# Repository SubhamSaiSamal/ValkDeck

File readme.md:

# VALKDECK 

Hey there, I'm Subham, a 14 year old kid (currently) from Chennai, India

I needed a better way to manage my flight sim telemetry, trigered automation workflows, and also blindly control my volume while locked into a game. I could have bought a generic macropad off Amazon for $20.

Instead, I spent 40 hours learning KiCad, routing my own custom PCB, designing an enclosure in onshape, and writing a CircuitPython program from scratch.

Welcome to *ValkDeck.*

It's a 9-key, fully hotswappable cyberdeck module powered by a Raspberry Pi Pico. It features per=key WS2812B underglow, a rotary encoder for media control, and a 0.91" I2C OLED display that feeds back live system status so I can actually know what my macros are doing.

# FEATURE PIVOT

If you look at the top right of the board, you'll see a machined metal blanking plug.

Originally, that 12mm hole was meant for a massive, avionics-grade MTS-101 toggle switch (the "Nuke Switch") to act as a hardware reset. I measured the top plate perfectly. What i *forgot* to measure was the internal Z-axis clearance. The massive rectangular block of the toggle switch slammed right into the PCB.

Physical reality remains undefeated. Instead of spending the next 6 hours rearranging the whole top-case, I pivoted. I covered it with a sleek metal plug for a premium industrial look. It's not a bug; it's an aesthetic hardware change.

[OnshapeCase](https://cad.onshape.com/documents/f17dd9f4e6cb3dbe968d54ad/w/35238b8d1c489f2cc410f163/e/0b39d0bd7ba726a80e99828b)

# THE PCB

I have been familiar with breadboards and scary jumper wire connections for quite a while. Instead of a terrifying 3D web of hand-soldered jumper wires, ValkDeck runs on a custom-routed, two layer FR-4 board.

Bottom-Mount SMD     : The kailh hotswap sockets and 1N4148 diodes are all surface mounted on the upperside of the board. 
Ghost-Free Matrix    : The diodes are correctly routed (Row to Column) to ensure complete N-key rollover without ghosting.
Through-Hole Anchors : The Raspberry Pi Pico, Rotary Encoder, and OLED screen are all through-hole soldered for maximum regidity 💪.

# HARDWARE

ValkDeck runs on a custom FR-4 PCB with a proper diode-protected switch matrix.

- The Brain   : Raspberry Pi Pico (RP2040)
- The Matrix  : 9x Kailh Hotswap Sockets (with 1N914 diodes pointing Row -> Col)
- The Display : 0.91" SSD1306 OLED (128x32)
- The Input   : 9x Mechanical Switches 
                 1x M274 Rotary Encoder (with push-to-mute)
- The RGB     : 9x WS2812B NeoPixels
- The Alert   : 1x Active Buzzer for audio feedback (and 8 bit pokemon and mario sfx)

# PINOUT ARCHITECTURE

If you're trying to understand the exact tracing or trying to make your very own ValkDeck, here is the routing:

| Component         | Pico Pin (GPIO)                              | Note                            |
| :---------------- | :------------------------------------------: | ------------------------------: |
| Matrix Rows       | GP09, GP10, GP11                             | Row 0,1,2                       |
| Matrix Cols       | GP00, GP01, GP02                             | Col 0,1,2                       |
| Encoder           | GP04(A), GP03(B), GND(C), GND(S2), GP05(S1)  | Volume sweeping and mute        |
| OLED              | GP16(SCL), GP17(SDA)                         | Standard I2C                    |
| NeoPixels         | GP15                                         | Single data line for all 9 LEDs | 
| Buzzer            | GP19                                         | PWM Audio (retro pokemon)       |

# RUNNING THE FIRMWARE

ValkBlox is run using Adafruit's CircuitPython. It uses the keypad library for the background matrix scanning, and displayio to dynamically update the OLED based on what macro you just fired

To Deploy : 

- Flash your Pico with the latest [CircuitPython.uf2](https://learn.adafruit.com/welcome-to-circuitpython/installing-circuitpython) 

- Grab the [Adafruit Library Bundle](https://github.com/adafruit/Adafruit_CircuitPython_Bundle) and drop this stuff into your CITCUITPY/lip folder
  - adafruit_hid
  - adafruit_displayio_ssd1306.mpy
  - adafruit_display_text
  - neopixel.mpy

- Drop firmware.py from this repo to the root drive

# BOM (Bill of materials)
|Name	                                                    |Purpose	                                                    |Quantity	|Total Cost (USD)	|Link	        |Distributor   |
| :------------------------------------------------------ | :---------------------------------------------------------: | ------- | --------------- | ----------- |----------------
|Raspberry Pi PICO                                          |Microcontroller (Controls everything lol)	                    |1	        |$4.05	            |[View Product](https://www.silverlineelectronics.in/products/raspberry-pi-pico?_pos=3&_sid=a84e46afc&_ss=r#)	 |Silverzone   |
|0.91 Inch I2C OLED                                      	|OLED Display to display backend info      	                    |1	        |$1.94	            |[View Product](https://roboticsdna.in/product/0-91-inch-iic-4-pin-oled-display-module-ssd1306-white/)	|RoboticsDNA   |
|Cherry MX RGB Switch	                                    |Brown RBG Switch (Pack of 10)                               	|1	        |$3.7	            |[View Product](https://meckeys.com/shop/accessories/keyboard-accessories/key-switches/cherry-mx-rgb-switch/?attribute_pa_cherry-mx=brown-rgb)	|Meckeys   |
|Kalih Socket                                               |Hot-Swap socket for cherry mx switches (Pack of 10)            |1	        |$0.84	            |[View Product](https://meckeys.com/shop/accessories/keyboard-accessories/key-switches/kailh-hot-swap-socket/)	|Meckeys   |
|Deep Purple Keycaps                                        |Purple Keycaps (Pack of 5)                                     |2	        |$2.00	            |[View Product](https://meckeys.com/shop/accessories/keyboard-accessories/keycaps/blank-dsa-keycaps-1u/?attribute_pa_variations=deep-purple)	|Meckeys   |
|Rotary Encoder            	                                |M274 Rotary Encoder Switch                                     |1	        |$0.46	            |[View Product](https://robu.in/product/m274-360-degree-rotary-encoder-module-brick-sensor)	|Robu   |
|rotary encoder knob           	                            |3D printed                                                     |1	        |----	            |-----       	|-----   |
|100nF capacitor           	                                |100nF ceramic capacitor (Pack of 25)                           |1	        |$0.15	            |[View Product](https://roboticsdna.in/product/0-1-uf-ceramic-capacitor-10-pieces/)	|roboticsDNA   |
|1N4148 Diode                                               |IN4148 DIODE (Pack of 10)                                      |2	        |$0.50              |[View Product](https://roboticsdna.in/product/diode-1n4148/)	|RoboticsDNA   |
|WS2812B RGB                    	                        |WS2812B 5050RGB (Pack of 10)                                   |1	        |$2.43	            |[View Product](https://robu.in/product/ws2812b-rgb-addressable-led-module)	|Robu   |
|AC1255 Buzzer           	                                |Buzzer                                                         |1	        |$0.074	            |[View Product](https://robu.in/product/ac1255-cldz-piezoelectric-passive-buzzer-1-25v12x5-5mm)	|Robu   |
|2.54mm male header          	                            |Male header for PICO                                           |2          |$0.55	            |[View Product](https://robu.in/product/ds1029-01-1x40p8bva1-b-connfly-1x40-pin-2-54mm-pin-header-single-row-stack-v-t-type)	|Robu   |
|Custom PCB                                           	 |Custom PCB printed from JLCPCB (includes shipping)                   |5	        |$9.20	            |[View Product](https://www.silverlineelectronics.in/products/raspberry-pi-pico?_pos=3&_sid=a84e46afc&_ss=r#)	 |Silverzone   |
|Total                      	                            |-----                                                          |0          |$25.82            |-----      	|-----   |

(ps. this repo will be updated to v1.1 after i build this board irl, stay tuned! :3)

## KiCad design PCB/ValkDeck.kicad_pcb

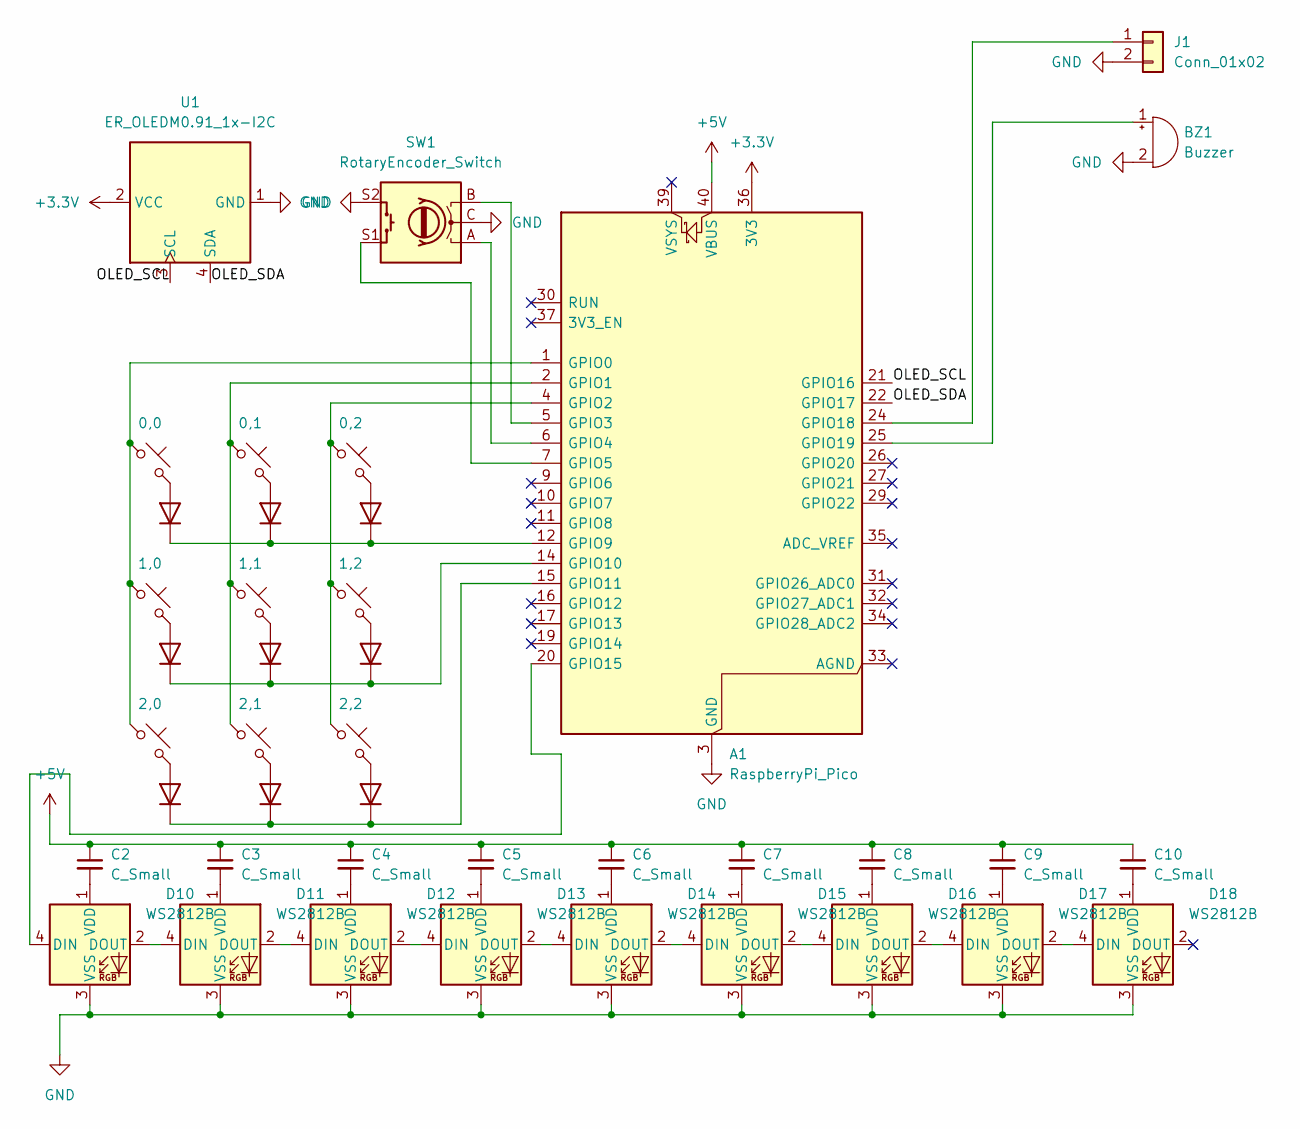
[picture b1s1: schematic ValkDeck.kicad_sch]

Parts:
A1: RaspberryPi_Pico; RaspberryPi_Pico_Common_Unspecified
BZ1: Buzzer; Buzzer_12x9.5RM7.6
C2, C3, C4, C5, C6, C7, C8, C9, C10: C_Small; C_Disc_D5.0mm_W2.5mm_P5.00mm
D1, D2, D3, D4, D5, D6, D7, D8, D9: 1N914; D_DO-35_SOD27_P7.62mm_Horizontal
D10, D11, D12, D13, D14, D15, D16, D17, D18: WS2812B; LED_WS2812B_PLCC4_5.0x5.0mm_P3.2mm
J1: Conn_01x02; PinHeader_1x02_P2.54mm_Vertical
SW1: RotaryEncoder_Switch; RotaryEncoder_Alps_EC11E-Switch_Vertical_H20mm
U1: ER_OLEDM0.91_1x-I2C
a2: 1,1; SW_MX_HS_CPG151101S11_1u
a3: 2,1; SW_MX_HS_CPG151101S11_1u
a4: 1,2; SW_MX_HS_CPG151101S11_1u
a5: 2,2; SW_MX_HS_CPG151101S11_1u
a6: 1,0; SW_MX_HS_CPG151101S11_1u
a7: 2,0; SW_MX_HS_CPG151101S11_1u
a8: 0,0; SW_MX_HS_CPG151101S11_1u
a9: 0,1; SW_MX_HS_CPG151101S11_1u
a10: 0,2; SW_MX_HS_CPG151101S11_1u

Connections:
+3.3V: A1.36 (3V3), U1.2 (VCC)
+5V: A1.40 (VBUS), C2.1, C3.1, C4.1, C5.1, C6.1, C7.1, C8.1, C9.1, C10.1
/OLED_SCL: A1.21 (GPIO16), U1.3 (SCL)
/OLED_SDA: A1.22 (GPIO17), U1.4 (SDA)
GND: A1.3 (GND), A1.8 (GND), A1.13 (GND), A1.18 (GND), A1.23 (GND), A1.28 (GND), A1.38 (GND), BZ1.2 (-), D10.3 (VSS), D11.3 (VSS), D12.3 (VSS), D13.3 (VSS), D14.3 (VSS), D15.3 (VSS), D16.3 (VSS), D17.3 (VSS), D18.3 (VSS), J1.2, SW1.C, SW1.S2, U1.1 (GND)
unnamed: A1.1 (GPIO0), a6.1, a7.1, a8.1
unnamed: A1.2 (GPIO1), a2.1, a3.1, a9.1
unnamed: A1.4 (GPIO2), a4.1, a5.1, a10.1
unnamed: A1.5 (GPIO3), SW1.B
unnamed: A1.6 (GPIO4), SW1.A
unnamed: A1.7 (GPIO5), SW1.S1
unnamed: A1.12 (GPIO9), D1.1 (K), D2.1 (K), D3.1 (K)
unnamed: A1.14 (GPIO10), D4.1 (K), D5.1 (K), D6.1 (K)
unnamed: A1.15 (GPIO11), D7.1 (K), D8.1 (K), D9.1 (K)
unnamed: A1.20 (GPIO15), D10.4 (DIN)
unnamed: A1.24 (GPIO18), J1.1
unnamed: A1.25 (GPIO19), BZ1.1 (+)
unnamed: D1.2 (A), a8.2
unnamed: D2.2 (A), a9.2
unnamed: D3.2 (A), a10.2
unnamed: D4.2 (A), a6.2
unnamed: D5.2 (A), a2.2
unnamed: D6.2 (A), a4.2
unnamed: D7.2 (A), a7.2
unnamed: D8.2 (A), a3.2
unnamed: D9.2 (A), a5.2
unnamed: D10.2 (DOUT), D11.4 (DIN)
unnamed: C2.2, D10.1 (VDD)
unnamed: D11.2 (DOUT), D12.4 (DIN)
unnamed: C3.2, D11.1 (VDD)
unnamed: D12.2 (DOUT), D13.4 (DIN)
unnamed: C4.2, D12.1 (VDD)
unnamed: D13.2 (DOUT), D14.4 (DIN)
unnamed: C5.2, D13.1 (VDD)
unnamed: D14.2 (DOUT), D15.4 (DIN)
unnamed: C6.2, D14.1 (VDD)
unnamed: D15.2 (DOUT), D16.4 (DIN)
unnamed: C7.2, D15.1 (VDD)
unnamed: D16.2 (DOUT), D17.4 (DIN)
unnamed: C8.2, D16.1 (VDD)
unnamed: D17.2 (DOUT), D18.4 (DIN)
unnamed: C9.2, D17.1 (VDD)
unnamed: C10.2, D18.1 (VDD)

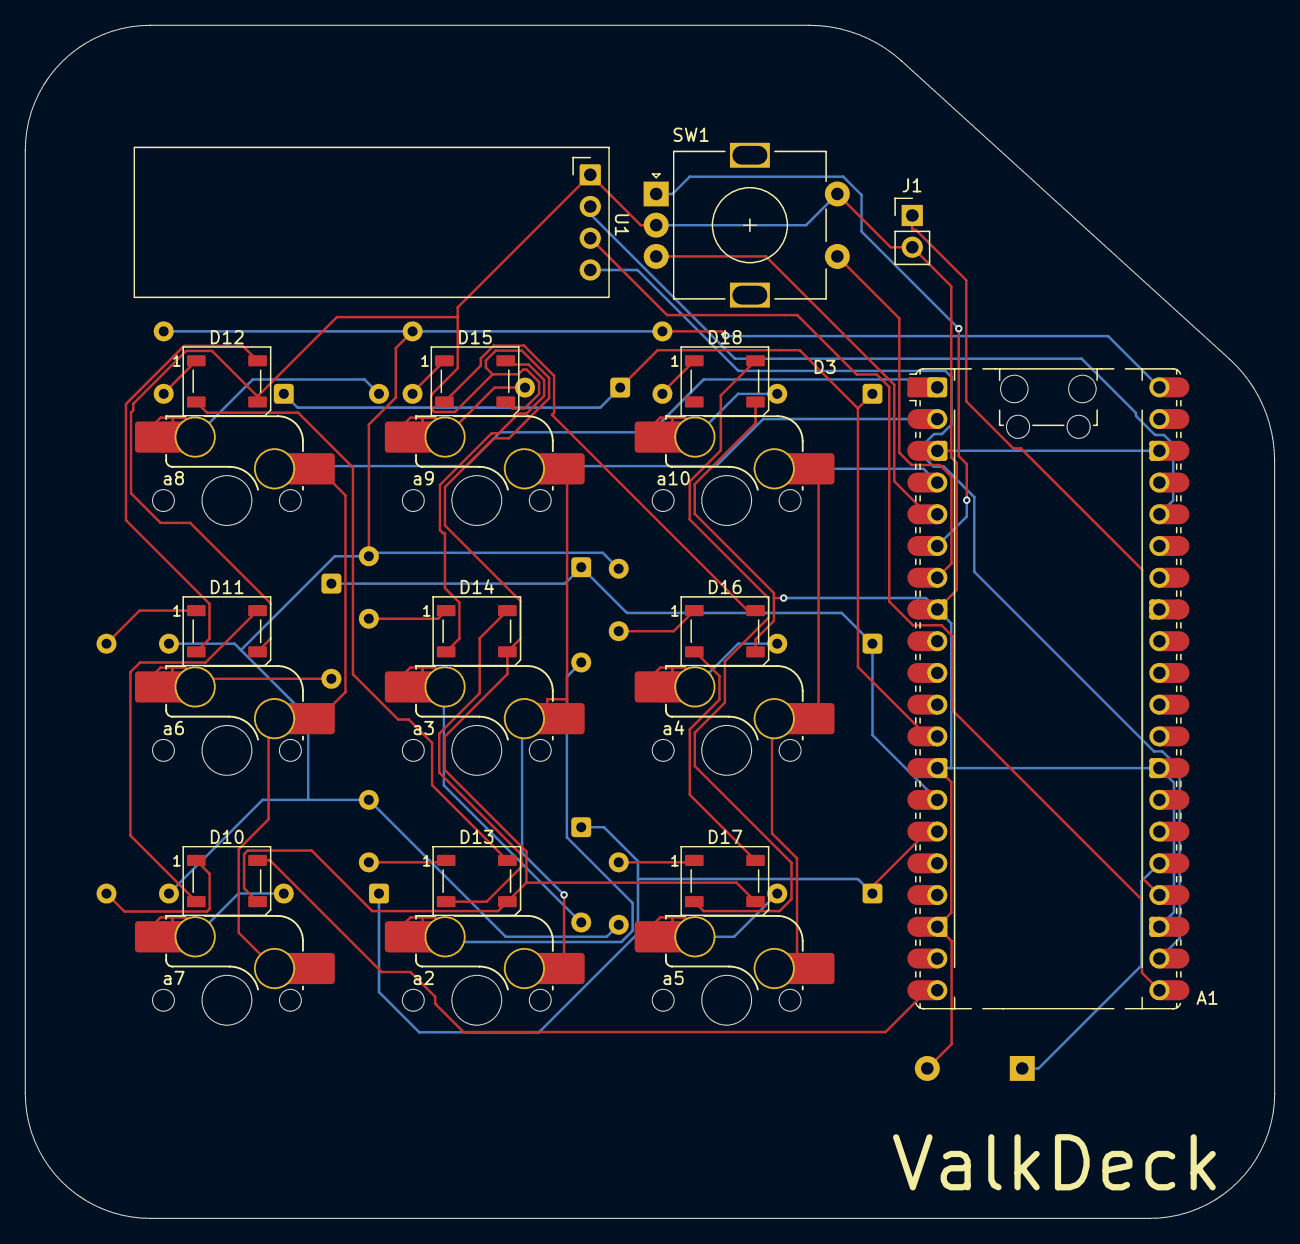
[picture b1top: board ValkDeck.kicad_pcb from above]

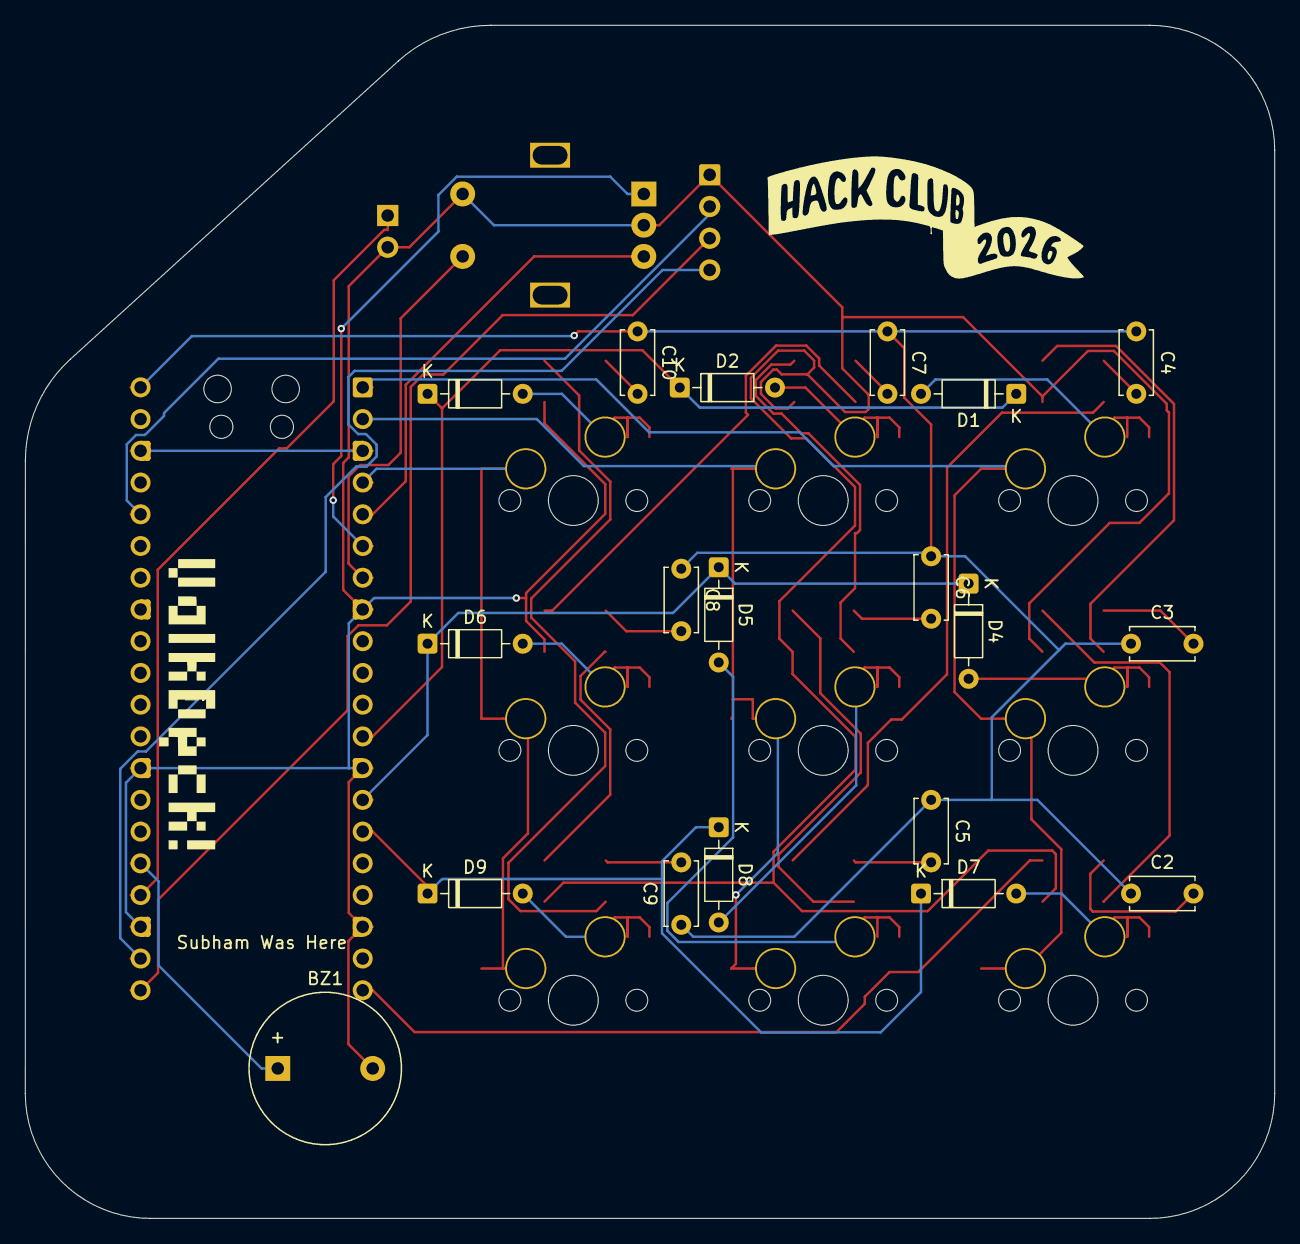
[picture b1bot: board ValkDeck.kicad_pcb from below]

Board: 2 copper layers, 100.0 x 95.5 mm, 43 parts (21 on the bottom side), 43 nets.

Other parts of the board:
g: LOGO; bannerfinal
i: LOGO; valkdeckie

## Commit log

2026-05-10 organized assets
2026-05-10 removed duplicates
2026-05-10 changes in readme
2026-05-10 new file images
2026-05-10 Replace local image with hosted URL in readme
    Updated the ValkDeck image to use a hosted URL.
2026-05-10 Fix image syntax in readme.md
    Updated the image syntax in the readme file.
2026-05-10 Replace images with links in README
2026-05-10 Enhance readme with more images of ValkDeck
    Added additional images to the readme for better visual representation of the ValkDeck features and PCB.
2026-05-11 added Onshape link
